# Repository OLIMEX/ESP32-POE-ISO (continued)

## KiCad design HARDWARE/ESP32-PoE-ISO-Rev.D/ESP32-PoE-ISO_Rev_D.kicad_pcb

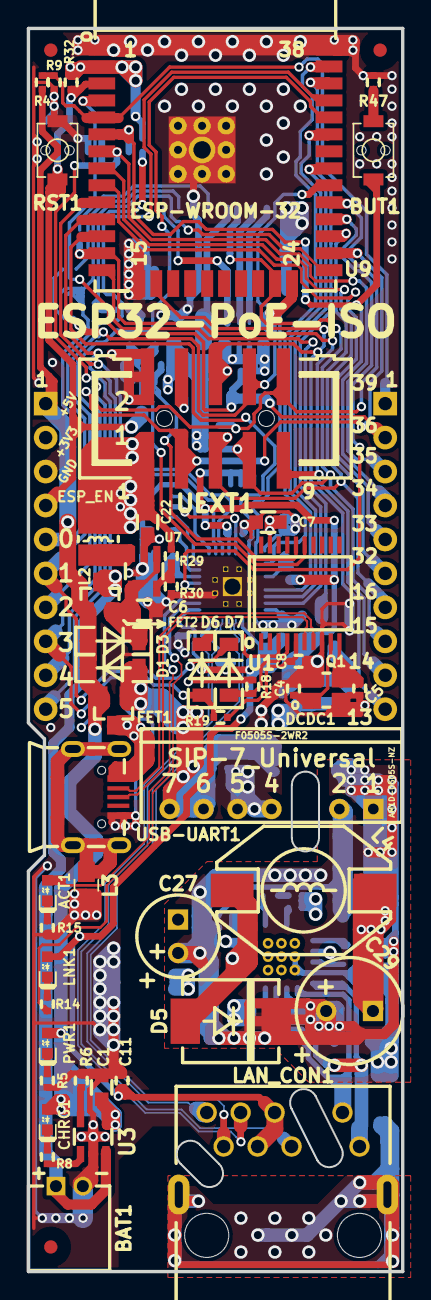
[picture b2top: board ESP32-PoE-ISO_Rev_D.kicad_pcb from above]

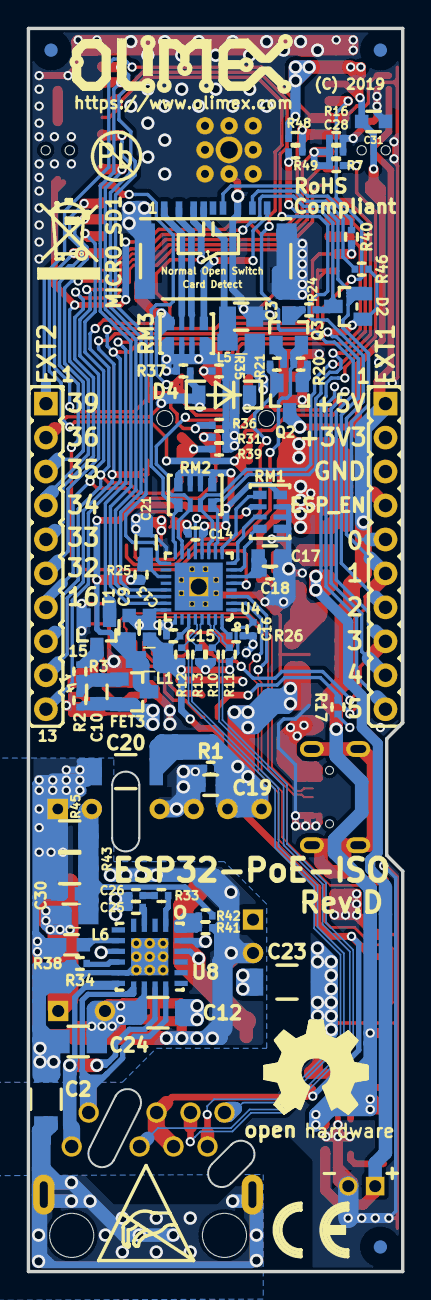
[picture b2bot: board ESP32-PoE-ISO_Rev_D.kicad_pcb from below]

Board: 4 copper layers, 28.0 x 93.0 mm, 133 parts (78 on the bottom side), 96 nets.

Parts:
ACT1: LED/YELLOW/0603; LED_0603_KA
BAT1: DW02R; LIPO_BAT-CON2DW02R
BUT1: IT1185AU2; IT1185AU2_V2
C1, C6, C7, C9, C10, C13, C19, C22, C30: 22uF/6.3V/20%/X5R/C0603; C_0603_5MIL_DWS
C2: 1nF/2000V/10%/X7R/C1206; C_1206_5MIL_DWS_ISO
C3: 47uF/6.3V/20%/X5R/C0805; C_0805_5MIL_DWS
C4, C5: 27pF/50V/5%/C0G/C0402; C_0402_5MIL_DWS
C8, C11, C14, C15, C16, C18, C25: 100nF/16V/10%/X7R/C0402; C_0402_5MIL_DWS
C12: 2.2uF/100V/20%/X7R/C1206(AVX_12061C225KAT2A_Comet); C_1206_5MIL_DWS_ISO
C17: 2.2uF/6.3V/10%/X5R/C0603; C_0603_5MIL_DWS
C20, C23: 1.0nF/3kV/10%/X7R/SMD/1808(VISHAY-VJ1808Y102KBHAT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; C_1808(4520)_5MIL_DWS_ISO
C21: NA(10uF/6.3V/20%/X5R/C0603); C_0603_5MIL_DWS
C24: 100nF/100V/20%/C1206; C_1206_5MIL_DWS
C26, C28: 1nF/50V/10%/X7R/C0402; C_0402_5MIL_DWS
C27: 15uF/100V/20%/RM2.5/6.3x11mm(Farnell:1281844); CPOL-RM2.5mm_6.3x11mm_PTH
C29: 680uF/10V/20%/105C/RM3.5/8x11.5mm; CPOL-RM3.5mm_8.0x11.5mm_PTH
C31: 1uF/10V/20%/X5R/C0603; C_0603_5MIL_DWS
CE_Sign: CE_Sign
CHRG1: LED/YELLOW/0603; LED_0603_KA
D1, D3, D6, D7: 1N5819S4/SOD123; SOD-123_1C-2A_KA
D2: BAT54C(SOT23-3); SOT23-3
D4: 1N5819S4/SOD-123; SOD-123_1C-2A_KA
D5: SS510/100V/5A/0.85V/DO214AB(SMC); DO214AB(SMC)_1(K)-2(A)
DCDC1: F0505S-2WR2(SIP-7); SIP-7_Universal
Drill_Slot1, Drill_Slot2, Drill_Slot3: 2 mm; Mounting_hole_2_mm
EXT1, EXT2: NS(HN1x10); HN1x10
FET1, FET2, FET3: WPM2015-3/TR; SOT23
FID1, FID2, FID3, FID4, FID5, FID6: Fiducial; Fiducial1x3
L1, L3, L5, L6: FB0805/600R/2A; L_0805_5MIL_DWS
L2: 2.2uH/1.5A/DCR=72mR/20%/3.00x3.00x1.50mm/CD32(NR3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; CD32
L4: 33uH/2.1A/DCR=0.1R/20%/DBS135(PD3316MT330); DBS135
LAN_CON1: RJP-003TC1(LPJ4112CNL)---Pin<7>_and_<8>_to_be_CUT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; RJP-003TC1(LPJ4112CNL)-ISO(Pin(7)and(8)CUT)
LNK1: LED/GREEN/0603; LED_0603_KA
Logo_OSHW: LOGO_OPENHARDWARE_8x8
Logo_Olimex: OLIMEX_LOGO_TB
MICRO_SD1: TFC-9P-1.7H(ATFFS150A01BR016); uSD(TFC-9P-1.xH(ATFFS150A01BR016))
PWR1: LED/RED/0603; LED_0603_KA
Q1: Q12MHz/20pF/10ppm/4P/3.2x2.5mm; TSX-3.2x2.5mm_GND(3)
Q2, Q3: BC817-40(SOT23); SOT23
R1, R2, R6, R18, R19, R25, R32, R36, R37, R39, R48: 10k/R0402; R_0402_5MIL_DWS
R3, R20, R21: 1k/R0402; R_0402_5MIL_DWS
R4, R33: 47k/R0402; R_0402_5MIL_DWS
R5, R8, R14, R15, R31, R35: 2.2k/R0402; R_0402_5MIL_DWS
R7, R16: 470k/R0402; R_0402_5MIL_DWS
R9: 100k/R0402; R_0402_5MIL_DWS
R10, R11, R12, R13: 49.9R/1%/R0402; R_0402_5MIL_DWS
R17: NA; R_0402_5MIL_DWS
R24, R46, R47: 220R/R0402; R_0402_5MIL_DWS
R26: 12.1k/1%/R0402; R_0402_5MIL_DWS
R29: 220k/R0402; R_0402_5MIL_DWS
R30: 49.9k/1%/R0402; R_0402_5MIL_DWS
R34: NA(49.9R/1%/R0402); R_0402_5MIL_DWS
R38: 25.5k/1%/R0603; R_0603_5MIL_DWS
R40: 10R/R0402; R_0402_5MIL_DWS
R41: 1.05k/1%/R0402; R_0402_5MIL_DWS
R42: 3.01k/1%/R0402; R_0402_5MIL_DWS
R43, R45: 220R/5%/0.25W/R1206; R_1206_5MIL_DWS
R49: NA/R0402; R_0402_5MIL_DWS
RM1, RM2, RM3: RA1206_(4X0603)_4B8_2.2k; R_MATRIX_4
RST1: IT1185AU2; IT1185AU2_V2
Sign_Antistatic: Val**; LOGO_ANTISTATIC_1
Sign_PB-Free: LOGO_PBFREE
Sign_RecycleBin: LOGO_RECYCLEBIN_1
T1: DTC114YKA(SOT-23); SOT23
U1: CH340T(SSOP20W); SSOP-20W
U3: BL4054B-42TPRN(SOT23-5); SOT-23-5
U4: LAN8710A-EZC(QFN32); QFN32_EP(33)_5.00x5.00x0.90mm_Pitch_0.50mm
U7: SY8089AAAC(SOT23-5); SOT-23-5
U8: Si3402-B-GM(QFN-20_5x5mm); QFN-20_5x5mm(Si3402-B-GM)
U9: ESP32-WROOM-32D-4MB; ESP-WROOM-32_MODULE
UEXT1: P-B-V-10-LF; GBH-254-SMT-10
USB-UART1: MISB-SWMM-5B-LF(USB_MICRO); USB-MICRO_MISB-SWMM-5B_LF

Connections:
+3.3VLAN: C9.1, C14.1, FET3.3, L1.1, R25.2, RM1.4.1, RM2.1.1, RM2.2.1, RM2.3.1, RM2.4.1, U4.12
+3V3: C10.1, C22.1, EXT1.2, FET3.2, L2.2, L5.1, R2.1, R17.1, R29.2, R31.1, R32.1, R35.1, R36.1, R37.1, R39.1, R48.1, RM3.1.2, RM3.2.2, RM3.3.2, RM3.4.2, U9.2, UEXT1.1
+5V: C1.1, CHRG1.2, D1.1, D3.2, EXT1.1, FET1.2, FET2.1, PWR1.2, R4.1, U3.4
+5VP: C19.1, C20.1, D1.2, DCDC1.6, DCDC1.7, FET1.1, R1.1
/+5V_USB: C7.1, FET1.3, R18.1, U1.19, USB-UART1.1
/D_Com: D2.3, R24.2, R49.2
/ESP_EN: C31.1, EXT1.4, Q2.3, R32.2, RST1.1, U9.3
/GPI34/BUT1: BUT1.1, EXT2.4, R48.2, R49.1, U9.6
/GPI35: C28.1, EXT2.3, R7.2, R16.1, U9.7
/GPI36/U1RXD: D4.2, EXT2.2, R37.2, U9.4
/GPI39: EXT2.1, R4.2, R9.1, U9.5
/GPIO0: D2.2, EXT1.5, U9.25
/GPIO1/U0TXD: D7.1, EXT1.6, U9.35
/GPIO2/HS2_DATA0: D2.1, EXT1.7, R46.1, RM3.4.1, U9.24, UEXT1.8
/GPIO3/U0RXD: D6.2, EXT1.8, R17.2, R19.2, U9.34
/GPIO4/U1TXD: EXT1.9, U9.26, UEXT1.3
/GPIO5/SPI_CS: EXT1.10, R36.2, U9.29, UEXT1.10
/GPIO12/PHY_PWR: T1.1, U9.14
/GPIO13/I2C-SDA: EXT2.10, R35.2, U9.16, UEXT1.6
/GPIO14/HS2_CLK: EXT2.9, R40.1, U9.13, UEXT1.9
/GPIO15/HS2_CMD: EXT2.8, MICRO_SD1.3, R39.2, U9.23, UEXT1.7
/GPIO16/I2C-SCL: EXT2.7, R31.2, U9.27, UEXT1.5
/GPIO17/EMAC_CLK_OUT_180: U4.5, U9.28
/GPIO18/MDIO(RMII): RM2.4.2, U4.16, U9.30
/GPIO19/EMAC_TXD0(RMII): U4.22, U9.31
/GPIO21/EMAC_TX_EN(RMII): U4.21, U9.33
/GPIO22/EMAC_TXD1(RMII): U4.23, U9.36
/GPIO23/MDC(RMII): U4.17, U9.37
/GPIO25/EMAC_RXD0(RMII): RM2.2.2, U4.11, U9.10
/GPIO26/EMAC_RXD1(RMII): RM2.1.2, U4.10, U9.11
/GPIO27/EMAC_RX_CRS_DV: RM2.3.2, U4.15, U9.12
/GPIO32: EXT2.6, U9.8
/GPIO33: EXT2.5, U9.9
/RD+: LAN_CON1.3, R11.2, U4.31
/RD-: LAN_CON1.6, R10.2, U4.30
/Shield: C2.2, LAN_CON1.0
/TD+: LAN_CON1.1, R13.2, U4.29
/TD-: LAN_CON1.2, R12.2, U4.28
/USB_D+: U1.6, USB-UART1.3
/USB_D-: U1.7, USB-UART1.2
/Vpos: C12.1, C20.2, C24.1, C27.1, C29.1, C30.1, D5.1, DCDC1.1, R38.2, R41.1, R43.1, R45.1, U8.12
/Vss: C12.2, C25.2, C26.2, C27.2, U8.7, U8.19
Earth: C2.1, C23.2, C24.2, R34.1, U8.9, U8.21
GND: BAT1.2, C1.2, C3.2, C4.2, C5.2, C6.2, C7.2, C8.2, C9.2, C11.2, C13.2, C14.2, C15.2, C16.2, C17.2, C18.2, C19.2, C21.1, C22.2, C23.1, C28.2, C31.2, DCDC1.4, DCDC1.5, EXT1.3, L3.2, MICRO_SD1.6, MICRO_SD1.CH1, Q1.3, R1.2, R5.2, R6.2, R9.2, R15.2, R16.2, R26.2, R30.2, R47.2, RM1.1.1, RM1.2.1, RM1.3.1, RST1.2, T1.2, U1.8, U3.2, U4.24, U4.25, U4.33, U7.2, U9.1, U9.15, U9.38, U9.39, UEXT1.2, USB-UART1.5
unnamed: ACT1.1, R15.1
unnamed: ACT1.2, U4.3
unnamed: BAT1.1, FET2.3, R7.1, U3.3
unnamed: BUT1.2, R47.1
unnamed: C3.1, L5.2, MICRO_SD1.4
unnamed: C4.1, Q1.1, U1.9
unnamed: C5.1, Q1.2, U1.10
unnamed: C6.1, D3.1, FET2.2, U7.1, U7.4
unnamed: C8.1, R19.1, U1.5
unnamed: C10.2, FET3.1, R2.2, R3.1
unnamed: C11.1, C13.1, C15.1, C16.1, L1.2, LAN_CON1.4, LAN_CON1.5, LNK1.2, R10.1, R11.1, R12.1, R13.1, U4.1, U4.27
unnamed: C17.1, C18.1, U4.6
unnamed: C21.2, R25.1, U4.19
unnamed: C25.1, U8.3
unnamed: C26.1, R33.1
unnamed: C29.2, L4.2, L6.1
unnamed: C30.2, DCDC1.2, L6.2, R42.2, R43.2, R45.2
unnamed: CHRG1.1, R8.1
unnamed: D4.1, UEXT1.4
unnamed: D5.2, L4.1, U8.18
unnamed: D6.1, U1.3
unnamed: D7.2, R18.2, U1.4
unnamed: L2.1, U7.3
unnamed: L3.1, USB-UART1.0
unnamed: LNK1.1, R14.1
unnamed: MICRO_SD1.1, RM3.3.1
unnamed: MICRO_SD1.2, RM3.2.1
unnamed: MICRO_SD1.5, R40.2
unnamed: MICRO_SD1.7, R46.2
unnamed: MICRO_SD1.8, RM3.1.1
unnamed: PWR1.1, R5.1
unnamed: Q2.1, R20.2
unnamed: Q2.2, R21.1, U1.16
unnamed: Q3.1, R21.2
unnamed: Q3.2, R20.1, U1.15
unnamed: Q3.3, R24.1
unnamed: R3.2, T1.3
unnamed: R6.1, U3.5
unnamed: R8.2, U3.1
unnamed: R14.2, U4.2
unnamed: R26.1, U4.32
unnamed: R29.1, R30.1, U7.5
unnamed: R33.2, U8.1
unnamed: R34.2, U8.8
unnamed: R38.1, U8.6
unnamed: R41.2, R42.1, U8.20
unnamed: RM1.1.2, U4.7
unnamed: RM1.2.2, U4.8
unnamed: RM1.3.2, U4.13
unnamed: RM1.4.2, U4.9
Spare1: LAN_CON1.9, U8.11, U8.14
Spare2: LAN_CON1.10, U8.10, U8.13

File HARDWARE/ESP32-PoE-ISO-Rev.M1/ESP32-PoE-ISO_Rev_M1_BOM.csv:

"Id";"Designator";"Footprint";"Quantity";"Designation";"Supplier and ref";
1;"FID3,FID2,FID6,FID5";"Fiducial1x3";4;"Fiducial";;;
2;"R32,R6,R18,R19,R48,R37,R39,R2,R25,R1,R36";"R_0402_5MIL_DWS";11;"10k/R0402";;;
3;"BUT1,RST1";"IT1185AU2_V2";2;"IT1185AU2";;;
4;"C1,C6,C22,C7,C19,C10,C9,C13";"C_0603_5MIL_DWS";8;"22uF/6.3V/20%/X5R/C0603";;;
5;"U3";"SOT-23-5";1;"TP4054-42-SOT25-R(SOT23-5)";;;
6;"R4";"R_0402_5MIL_DWS";1;"47k/R0402";;;
7;"R9";"R_0402_5MIL_DWS";1;"100k/R0402";;;
8;"CHRG1,ACT1";"LED_0603_KA";2;"LED/YELLOW/0603";;;
9;"PWR1";"LED_0603_KA";1;"LED/RED/0603";;;
10;"R5,R14,R15,R8,R31,R35";"R_0402_5MIL_DWS";6;"2.2k/R0402";;;
11;"FID1,FID7,FID4,FID8";"Fiducial1x3_Paste";4;"Fiducial";;;
12;"C11,C8,C18,C16,C15,C14";"C_0402_5MIL_DWS";6;"100nF/10V/20%/X5R/C0402";;;
13;"FET1,FET2,FET3";"SOT23";3;"IRLML6402TRPbF";;;
14;"L2";"L_2016_MM";1;"1.0uH/4.2A/DCR=35mR/20%/2.00x1.60x1.00mm/L2016(PIM201610-1R0MTS00)";;;
15;"R30";"R_0402_5MIL_DWS";1;"49.9k/1%/R0402";;;
16;"R29";"R_0402_5MIL_DWS";1;"220k/R0402";;;
17;"U7";"SOT-563-6";1;"TPS62A02ADRLR(SOT-563-6)";;;
18;"LNK1";"LED_0603_KA";1;"LED/GREEN/0603";;;
19;"L3,L5,L1";"L_0805_5MIL_DWS";3;"FB0805/600R/2A";;;
20;"DCDC1";"SIP-7_Universal";1;"F0505S-2WR2(SIP-7)";;;
21;"C27";"CPOL-RM2.5mm_6.3x11mm_PTH";1;"15uF/100V/20%/RM2.5/6.3x11mm(Farnell:1281844)";;;
22;"U1";"MSOP-10_Pitch-0.5mm_3.00x3.00x1.00mm";1;"CH340X(MSOP-10)";;;
23;"D6,D7,D3,D1,D4,D9";"SOD-123_1C-2A_KA";6;"1N5819S4/SOD123";;;
24;"R17,R49";"R_0402_5MIL_DWS";2;"NA/R0402";;;
25;"USB-UART1";"USB-MICRO_MISB-SWMM-5B_LF";1;"MISB-SWMM-5B-LF(USB_MICRO)";;;
26;"TVS1";"SOT-23-5";1;"ESDS314DBVR(SOT-23-5)";;;
27;"LAN_CON1";"RJP-003TC1(LPJ4112CNL)";1;"RJP-003TC1(LPJ4112CNL)";;;
28;"UEXT1";"GBH-254-SMT-10";1;"P-B-V-10-LF";;;
29;"R28";"R_1206_5MIL_DWS";1;"0.03R/1%/R1206";;;
30;"L4";"DBS135";1;"33uH/2.1A/DCR=0.1R/20%/DBS135(PD3316MT330)";;;
31;"C26";"CPOL-RM2.5mm_6.3x11mm_PTH";1;"470uF/10V/20%/Low_ESR/RM2.5/6.0x11mm";;;
32;"R47,R46,R24";"R_0402_5MIL_DWS";3;"220R/R0402";;;
33;"C24,C12";"C_0603_5MIL_DWS";2;"100nF/100V/10%/X7R/C0603";;;
34;"D10";"SMA-KA";1;"SMAJ58A/SMA";;;
35;"U6";"ESP32-WROVER_MODULE";1;"ESP32-WROOM-32E-N4";;;
36;"MH1,MH2,MH3";"NPTH_2.2mm";3;"Mounting_Hole_NPTH";;;
37;"BAT1";"LIPO_BAT_VERTICAL_DW02S";1;"DW02S";;;
38;"R43";"R_0402_5MIL_DWS";1;"4.7k/R0402";;;
39;"C30";"C_0402_5MIL_DWS";1;"NA(120pF/50V/5%/C0G/C0402)";;;
40;"EXT2,EXT1";"HN1x10";2;"NS(HN1x10)";;;
41;"R40";"R_0402_5MIL_DWS";1;"10R/R0402";;;
42;"RM3,RM2,RM1";"R_MATRIX_4";3;"RA1206_(4X0603)_4B8_2.2k";;;
43;"C2";"C_1206_5MIL_DWS_ISO";1;"1nF/2000V/10%/X7R/C1206";;;
44;"C20";"C_1808(4520)_5MIL_DWS_ISO";1;"NA(1.0nF/3kV/10%/X7R/SMD/1808(VISHAY-VJ1808Y102KBHAT4X_Farnell-2407291))";;;
45;"C23";"C_1808(4520)_5MIL_DWS_ISO";1;"1.0nF/3kV/10%/X7R/SMD/1808(VISHAY-VJ1808Y102KBHAT4X_Farnell-2407291)";;;
46;"R3,R20,R21";"R_0402_5MIL_DWS";3;"1k/R0402";;;
47;"C21";"C_0603_5MIL_DWS";1;"NA(10uF/6.3V/20%/X5R/C0603)";;;
48;"C17";"C_0603_5MIL_DWS";1;"2.2uF/6.3V/10%/X5R/C0603";;;
49;"U4";"QFN32_EP(33)_5.00x5.00x0.90mm_Pitch_0.50mm";1;"LAN8710A-EZC(QFN32)";;;
50;"T1";"SOT23";1;"LMUN2211LT1G(SOT-23)";;;
51;"R12,R11,R10,R13";"R_0402_5MIL_DWS";4;"49.9R/1%/R0402";;;
52;"R16,R7";"R_0402_5MIL_DWS";2;"470k/R0402";;;
53;"R26";"R_0402_5MIL_DWS";1;"12.1k/1%/R0402";;;
54;"Q3,Q2";"SOT23";2;"BC817-40(SOT23)";;;
55;"D2";"SOT23-3";1;"BAT54C(SOT23-3)";;;
56;"TVS2,TVS3";"D_0402_5MIL_DWS";2;"NA(GG0402052R542P)";;;
57;"C3";"C_0805_5MIL_DWS";1;"47uF/6.3V/20%/X5R/C0805";;;
58;"D8";"DO214AA_1(K)-2(A)";1;"NA(SMBJ6.0A)";;;
59;"C25";"C_0402_5MIL_DWS";1;"12pF/50V/5%/COG/C0402";;;
60;"R22";"R_0402_5MIL_DWS";1;"24.9k/1%/R0402";;;
61;"R23";"R_0402_5MIL_DWS";1;"1.27k/1%/62.5mW/R0402";;;
62;"C28";"C_0402_5MIL_DWS";1;"1nF/50V/10%/X7R/C0402";;;
63;"R33";"R_0402_5MIL_DWS";1;"4.7R/R0402";;;
64;"D5";"DO214AB(SMC)_1(K)-2(A)";1;"SS510/100V/5A/0.85V/DO214AB(SMC)";;;
65;"R41,R27";"R_2512_MM_DWS";2;"9.1k/1W/R2512";;;
66;"U5";"ESOIC-8";1;"TX4138(ESOIC-8)";;;
67;"R34";"R_0402_5MIL_DWS";1;"10.5k/1%/R0402";;;
68;"C29";"C_0402_5MIL_DWS";1;"NA(100nF/10V/20%/X5R/C0402)";;;
69;"U8";"SOT-23-5";1;"NA(SN74LVC1G04DBVR(SOT23-5))";;;
70;"R42";"R_0402_5MIL_DWS";1;"NA(10R/R0402)";;;
71;"C31";"C_0603_5MIL_DWS";1;"1uF/10V/10%/X5R/C0603";;;
72;"MICRO_SD1";"uSD(TFC-9P-1.xH(ATFFS150A01BR016))";1;"TFC-9P-1.7H(ATFFS150A01BR016)";;;
73;"R38";"R_0402_5MIL_DWS";1;"56.2k/1%/R0402";;;
74;"U2";"ESOIC-8";1;"TPS2378DDAR(HSOIC-8)";;;
75;"D11";"DO214AA_1(K)-2(A)";1;"SMBJ5.0A";;;

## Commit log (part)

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2019-04-12 Initial upload of ESP32-POE-ISO hardware files
2019-09-10 Update
    Revision C and 3D added
2020-06-22 Update
    Revision D
2020-10-27 Update
    Info about software examples
2021-07-08 Update
    Dimensions
2021-11-05 update
    new revision
2021-12-17 Update
    STEP export
2022-01-18 Update
    revision H
2022-07-14 Update
    Hardware revision I
2022-07-18 Update
    Added dimensions for upcoming revision J with mount holes
2022-11-15 Update
    Revisions J and K
2023-05-11 Update
    revision L files
2025-06-04 Update
    Added revision M
2026-01-05 adding 3d printed case
2026-05-06 Update
    Added hardware revision N and updated change log
2026-05-07 Update
    Added 3d design for EA variant case
